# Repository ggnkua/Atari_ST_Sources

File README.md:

# Atari ST source code repository

## What is it?

A repository collecting source code for the Atari ST, STE, Mega ST, Mega STE, STBook, STacy, TT030 and Falcon030 ([Wikipedia link](https://en.wikipedia.org/wiki/Atari_ST)).

## How to get it?

Just clone the repository. Make sure to init the submodules while cloning (```--recurse-submodules```) so that you get the code from linked repositories.

## How to use the code on this archive?

TODO (tl;dr: get some dev tools and dig in!)

## How can I contribute?

1. Upload your source somewhere and raise an issue
1. E-mail the maintainer (ggnkua [at] gmail [dot] com) with archive(s) of files and optionally the location of the archive the files should be placed
1. Fork the repository and create a pull request (note that the maintainer has no experience with this and is likely to mess up things. But hey we can try!)

# Verified to compile

## ASM

## C

|Location|Comment|
|--|--|
|`C/Alan Pratt/Gulam`|Compiles with Mark Williams C 3.0.5|
|`C/Michael Thänitz/7UP_PD`|Compiles with Pure C|
|`C/Markus Kohm/7UP_PD`|Compiles with Pure C|
|`C/Paradox/X-Debug`|Builds with Lattice C 5.6 and DevPac 3.1|

## GFA Basic

## Omikron Basic

## Pascal

## STOS

## Various

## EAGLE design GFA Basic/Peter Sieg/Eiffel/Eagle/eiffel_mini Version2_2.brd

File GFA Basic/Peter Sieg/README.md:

# Atari-ST

```
Aus Wikipedia:  

Der Atari ST war ein Heimcomputer von Atari aus dem Jahr 1985. Die ST/TT-Serie eignete sich allerdings auch für professionelle
Büroanwendungen. Die Abkürzung "ST" steht dabei für Sixteen/Thirty-Two (16/32), da der verwendete Hauptprozessor, der Motorola
68000, einen 16 Bit breiten Datenbus hat und intern mit 32 Bit arbeitet. Der Adressbus ist 24 Bit breit. 

Geschichte

Der Atari ST war eines der ersten verbreiteten Modelle mit einer grafischen Benutzeroberfläche, dem GEM von Digital Research;
der Hauptspeicher lag zwischen 512 kByte und einem MByte, diese Zahl wurde, nach Aufrunden, Teil der Modellbezeichnung (520 ST
- 512 KB; 1040 ST - 1024 KB = 1 MB). Einzige Ausnahmen bildeten der 260 ST (wurde mit 512 KB ausgeliefert) und der 520ST+ 
(1 MB). Der 260 ST sollte getreu seiner Bezeichnung auch nur mit 256 KB ausgeliefert werden. In der Endphase der Entwicklung 
stellte sich jedoch heraus, daß 256 KB definitiv nicht ausreichen würden, um den Rechner mit TOS sinnvoll zu betreiben. Da 
jedoch die Werbetrommeln bereits gerührt wurden, wurde er kurzerhand mit 512 KB ausgeliefert. Da er sich sonst kaum vom 520 ST 
unterschied, verschwand er sehr schnell vom Markt. Zusätzliche Buchstaben gaben weitere Ausstattungsmerkmale an, der 1040 STF 
besaß etwa ein internes 3,5"-Floppylaufwerk und der 1040 STFM einen TV-Modulator. Anfangs wurde der Atari ST mit dem 
Betriebssystem auf Diskette ausgeliefert (TOS 1.0), spätere Modelle hatten das Betriebssystem fest im ROM eingebaut. Die Mega 
ST Serie besaß eine abgesetzte Tastatur und einen Hauptspeicher von bis zu 4 MB. Festplatten waren ebenfalls verfügbar (anfangs 
20 MB, MFM) und direkt an den Atari ST anschließbar (DMA-Port, auch ACSI-Port genannt). Der Atari ST besaß die Möglichkeit, 
entweder einen hochauflösenden Schwarzweiß-Monitor oder einen Farbmonitor mit geringerer Auflösung anzuschließen. Die 
Farbauflösung betrug 320×200 Pixel bei 16 Farben und 640×200 bei 4 Farben, jeweils aus einer Palette von 512 Farben. Der 
monochrome Monitor SM124 hatte eine Auflösung von 640×400 Pixeln bei 72 Hz Bildwiederholrate. Dies waren für die damalige Zeit 
hervorragende Werte, im PC-Sektor gab es gerade CGA, Hercules und für besonders teure Rechner EGA. Daher wurde der Rechner 
besonders im CAD- oder DTP-Bereich populär. Im deutschsprachigen Raum überwogen auch ansonsten eher Büroanwendungen wie 
Textverarbeitung oder Tabellenkalkulation. In den USA wurde der ST vorwiegend mit Farbmonitor eingesetzt und galt eher als 
Spiele- und Demomaschine (siehe: Atari Demos). Weltweit brachte dem Atari ST eine fest eingebaute MIDI-Schnittstelle eine weite 
Verbreitung bei Musikern und Tonstudios ein. Des Weiteren war der Atari ST sozusagen ein Mittler zwischen den Welten. Das 
Dateisystem der Disketten war mit dem von MS-DOS weitgehend kompatibel, so dass man beispielsweise Zugriff auf Textdateien 
hatte, die auf einem PC erstellt wurden. Es gab auch einen Apple-Emulator, und er wurde, mit entsprechender Software versehen, 
als intelligentes Terminal und Entwicklerstation an verschiedensten Mainframes und Mini-Computern von HP sowie Workstations von 
Texas Instruments und HP eingesetzt. Der Atari ST stand in Konkurrenz zum etwas später auf den Markt gekommenen Amiga 500 von 
Commodore. Als Nachfolgemodelle des Atari ST gab es noch den Atari TT, den 1040 STE, den Atari MegaSTE, den Laptop Atari STacy 
aber auch ein Notebook STBook und ab Anfang der 1990er den Falcon. Letzterer hatte dann aber keinen großen Markterfolg mehr. 
Mehrere Fachzeitschriften wie ST-Computer, ST-Format, ST-Magazin, TOS, XEST oder Atari Inside versorgten die Nutzer mit 
Informationen zu diesem Rechner. 

Hardware
Prozessor:             Motorola MC68000, 8 MHz 
Arbeitsspeicher:       512 bis 1 MB (max 4 MB über Speichererweiterungen von Drittanbietern möglich), 
                       von dem Speichercontrollerchip "MMU" verwaltet. 
Grafikchip:            "Shifter", benutzte eine Teil des Hauptspeichers als Bildspeicher, wird heutzutage als 
                       "Shared Memory Architektur" bezeichnet. Auflösungen und Farbtiefen siehe oben 
Blitter-Chip:          Erst ab 1040STFM, Unterstützung der CPU bei Grafik- und Speicheroperationen. 
                       Nachrüstung über Zusatz-Karten in allen ST-Modellen möglich. 
GLUE-Chip:             Systemlogik, die das System zusammenhält (Chip-Selects, Takt, etc.) 
Sound:                 Yamaha YM-2149, dreistimmiger Synthesizer-Chip mit Rauschgenerator 
Floppy-Controler:      WF1772: MFM-Controller für Laufwerke mit Standard-Shugart-Bus. 
DMA-Controller:        von Atari, steuert die ACSI-Schnittstelle (Atari Computer System Interface) an. 
                       ACSI ist eine auf Gruppe-1-Kommandos und einige Signale eingeschränkte SCSI-Schnittstelle. 
2x Motorola 6850:      Interface-Bausteine, 1x für die Midischnittstelle, 1x für die serielle Kommunikation mit der 
                       Tastatur 
MFP:                   68901 MFP (MultiFunctionPeripheral) u.a. für erweiterte Interruptlogik und serielle Schnittstelle 

Modelle
Modell    Jahr Merkmal 
260 ST    1985 Ur-ST mit Disketten-TOS, nur sehr kurz auf dem Markt 
520 ST    1985 Ur-ST mit Disketten-TOS 
520 STM   1985 ROM-TOS, TV-Anschluss - wurde später in 520 ST umbenannt
               Preis inkl. SF354+SM124 2.000DM (1.020€)
 
520 ST+   1985 1 MB RAM 
520 STF   1986 internes Diskettenlaufwerk 
520 STFM  1986 wie 520 STF, mit TV-Anschluss 
1040 STF  1986 wie 520 STF, 1 MB RAM 
               Preis inkl. SM124 ca. 3.300DM (1.700€)
 
1040 STFM 1986 wie 1040 STF, mit TV-Anschluss 
2080 ST   1986 „Prototyp“ - 2 MB RAM 
4160 ST   1986 „Prototyp“ - 4 MB RAM 
MEGA ST   1987 abgesetzte Tastatur, 1, 2 oder 4 MB RAM 
4160 STE  1988 „Prototyp“ - um Stereo, 2 Joypad-Ports, BLiTTER erweitert 
1040 STE  1989 Final Version des 4160 STE, nur 1 statt 4 MB RAM
               Preis ca. 1.300DM (660€)
 
520 STE   1989 Wie 1040 STE, 512 KB RAM 
1040 STE+ 1990 Prototyp - 1040 STE mit Festplatte und AT-Emulator 
TT 030    1990 68030-CPU/32 MHz, neues TOS 3.0 
Mega STE  1991 erweiterter Mega ST im TT-Gehäuse, TOS 2.0x, 16 MHz. Preis für 4MB Version: 2.800DM (1.400€)
 
FX-1      1991 Falcon-Prototyp mit TOS 2.07 
Falcon030 1992 68030-CPU/16 MHz, 56k-DSP, TOS 4.0x, 1040ST-Gehäuse
               Preis für 4MB+85MB HDD Version: 2.250DM (1.150€)
 
Falcon040 1993 „Prototyp“ - Falcon mit 040-CPU 
Microbox  1993 „Prototyp“ - Falcon im Desktop-Gehäuse 
Tragbare Modelle
Modell    Jahr Merkmal 
Stacy     1989 7,5 kg schwerer Laptop auf Basis des Mega ST 
ST Book   1991 Grundfläche eines DIN-A4-Blatts, knapp 2 kg leicht; ca. 1000 gebaute Einheiten 
ST Pad    1991 'Prototyp' - Pentop-Computer 

Tipps

PC Floppy's sind auf ID=1 eingestellt. Atari ST benötigen ID=0! Dies kann man umstellen (Jumper, Lötbrücke, etc.). 

Oft gestellte Frage: Wie bekomme ich die Dateien von meinem Windows-PC auf meinen Atari-ST? 

Oft hat der Windows-PC hat Probleme auf dem Atari ST formatierte Disketten zu lesen/schreiben. Die einfachste Lösung ist es die Disketten auf dem Windows-PC zu formatieren! Sollten Sie keine DD-Disketten auftreiben können, nehmen Sie HD-Disketten und kleben Sie das zweite Loch (das ohne Schreibschutz-Schieber) mit Klebeband ab.
Nun muß die Diskette nur noch als DD-Diskette formatiert werden. 

MS-DOS / Windows95/98:
In die Kommandozeile/DOS-Shell gehen und formatieren: format /F:720 a: 

Windows XP:
Leider kennt der format-Befehl unter Windows XP den obigen Parameter nicht mehr :-( Aber der folgende Aufruf tut das selbe: format /T:80 /N:9 a: 

Hi, die einseitigen Laufwerke gab es nur als Externe Laufwerke SF354..
Diese wurden 1985 mit den ersten 520ST ausgeliefert.. 

520ST 512kb mit Disk-Tos, im Rom nur ein Loader...
SF354 360k Einseitig...
Monochom Moni... 

Gesamt 3000.- DM 

kurze Zeit später wurden die ersten SF314 ausgeliefert.... 

Alle ST mit eingebauten Laufwerken waren dann 720k-Laufwerke... 

Disk mit mehr als 720k waren überformatiert..... 

Reparatur Tips

Leblos liegt er da, mehrfaches Ein- und Ausschalten ruft nur eine schwache binäre Reaktion hervor: die LED für die 
Betriebsanzeige signalisiert "Strom", oder eben nicht.
Nach kräftigem Schütteln des Patienten der erste Hoffnungsschimmer, der Monitor wird weiß. Dabei bleibt es leider auch. 
Also nochmal aus- und wiedereingeschaltet ... nichts. Der letzte zögerliche Kontaktversuch unseres digitalen Kameraden 
lässt sich offensichtlich nicht reproduzieren. Wie gut hat es dagegen der Bekannte X getroffen, der hat wenigstens Bomben 
auf dem Bildschirm, 'mal zwei, 'mal drei und manchmal eine ganze Reihe.
Diese Symptome offensichtlicher Altersschwäche sind in letzter Zeit immer häufiger geworden. Die Ratlosigkeit von 
Computerfachhändlern angesichts eines Atari-Rechners weckt nicht gerade Vertrauen in die Kompetenz derselben. Zudem 
rechtfertigt der Wiederbeschaffungswert beispielsweise eines 1040 ST von ca. DM 250,- in den seltensten Fällen 
dreistellige DM-Aufwendungen für die Reparatur. Also, Ärmel hoch, denn die Axt im Haus ...
Um Mißverständnissen vorzubeugen:
Schwerwiegende Defekte können auch nach Studium dieses Artikels nicht von Laien behoben werden. Es hat sich jedoch 
gezeigt, dass ca. 80% aller Funktionsstörungen sehr einfache Ursachen haben, die meist leicht behoben werden können. 
Hier soll gezeigt werden, wie man die eine oder andere Störung mit wenig Aufwand beseitigen kann.
Zur Sache
Hier einige häufige Fehler und deren vermutliche Ursache, in Klammern die Absätze, die man mindestens lesen sollte:
   1. Betriebsanzeige leuchtet nicht > Netzteil defekt (A, B1)
   2. Bildschirm bleibt schwarz > Kontakt /RAM-Fehler (A, C, D)
   3. Bildschirm bleibt weiß > Kontaktfehler (A, C)
   4. Pixelmüll > Kontakt /RAM-Fehler (A, C, D)
   5. Rechner stürzt bei Anfahren der Menüleiste ab (Mega ST) > Blitter (A, E)
   6. Rechner stürzt nach gewisser Zeit ab > Kontakt /RAM-Fehler (A, C, D, Netzteil B2)
   7. Rechner hängt bei Floppyzu griffen > Netzteil (A, B2)
   8. Uhr läuft nicht richtig, Rechner bombt willkürlich > Echtzeituhr (A, F) 
Noch ein Hinweis:
Rechner mit diversen Erweiterungen können auch diverse erweiterte Probleme mit sich bringen, auf die hier im Einzelnen 
nicht eingegangen wird. Sicher ist aber in jedem Fall, dass eine Hardwareerweiterung, gleich, welcher Art, nur in einem 
einwandfrei funktionierenden Rechner richtig arbeitet.
A: Öffnen des Rechners
Rechner auf den Rücken legen, alle Schrauben lösen und beiseite legen. Wieder umdrehen und Deckel abheben. Beim 260/520 
einfach nach oben weg, beim 1040 zuerst an der Seite ohne Floppy, beim Mega ST zuerst hinten und die Leitung zum 
Batteriefach abziehen. Es sollte keine Diskette im Laufwerk sein, damit der Auswurfhebel nicht stört.
Beim 260/520er und 1040er die Tastatur abziehen und die drei Schrauben an der vorderen Blechkante lösen. Die Platine des 
260/520ers ist noch mit drei weiteren Schrauben befestigt, die man durch Öffnungen im Abschirmblech erreicht, weg damit. 
Besitzer eines 1040 müssen die beiden Schrauben mit denen das Netzteil befestigt ist, lösen. Die Platine wird nun mitsamt 
Abschirmblechen aus dem Plastikunterteil gehoben.
Ein Mega ST kann in seiner Behausung verbleiben.
Jetzt mit einer Flachzange die Blechlaschen geradegebogen, bei 1040 und Mega ST ist auch eine unter der Floppy, und das 
obere Abschirmblech lässt sich abnehmen. Das Netzteil des 1040 ist dabei etwas im Wege, aber es ist zu schaffen.
Das war es, für den Zusammenbau einfach den Text rückwärts lesen.
B1: Das Netzteil
Wenn das Netzteil ausgefallen ist, sollte man sich nach einem Ersatz umsehen. Beim 520er ist der Trafo vergossen und 
deshalb unzugänglich, bei 1040 und Mega ST handelt es sich um Schaltnetzteile. Der Fachmann weiß: selbst wenn man ein 
defektes Bauelement findet und ersetzt, heißt das noch lange nicht, dass das gute Stück wieder funktioniert. Man kann 
bestenfalls die Sicherung überprüfen und bei Defekt ersetzen. Mir ist bisher allerdings noch kein Netzteil untergekommen, 
das durch Austausch einer defekten Sicherung wieder zu reaktivieren war, als einziges Ergebnis meiner Bemühungen hatte 
ich dann mehrere defekte Sicherungen.
B2:
Die Netzteilspannung sinkt offenbar mit zunehmendem Alter des Rechners ab. Wichtig ist vor allem, dass im 5Volt-Zweig die 
Spannung nicht zu niedrig ist.
Die meisten Bauelemente im Atari benötigen eine Spannung von minimal 4,5 V und maximal 5,5 V. Mit einem Handmultimeter 
lässt sich das überprüfen. Aber Achtung! Bei Floppyzugriffen sinkt die 5-Volt-Versorgungsspannung um ca. 0.4 Volt ab. Das 
bedeutet, das für einen sicheren Betrieb eine Spannung von 4,9 Volt anstehen muss.
Ein zu schlappes Netzteil kann auf folgende Weise getuned werden: man lasse sein Multimeter zur Kontrolle an der 
5 Volt-Versorgung hängen und suche ein Poti namens VR1. Wenn man eines gefunden hat, kann man damit die Spannung 
abgleichen. Leider läuft der 12 Volt-Zweig auch mit, so dass man zwischendurch auch dort 'mal die Spannung kontrollieren 
muss. Wenn 13 Volt überschritten werden, sollte eine Diode 1N4001 in die 12 Volt Leitung eingeschleift werden. Der 
Kathodenring in Richtung Board.
Wer in seinem Netzteil kein Poti findet weil keines da ist, muss parallel zu R14 einen Widerstand von 47K einlöten.
C: Kontaktfehler
Kontaktfehler sind die häufigste Ursache für "seltsame Erscheinungen". Ob es sich dabei um Oxydation, Verschmutzung oder 
ausgeleierte Kontakte handelt ist eigentlich egal, der Effekt ist immer der gleiche.
Bei einem weißen Bildschirm ist zumindest das RAM ansprechbar. Der Fehler ist aller Wahrscheinlichkeit nach bei den Roms 
zu suchen. Also, Spucke auf den Daumen und die "Brüder" kräftig in die Fassungen gedrückt.
Wenn man schon mal dabei ist, sollte man auf ein Nachdrücken der anderen Bauelemente nicht verzichten. Hat diese 
fachmännische Aktion keine Früchte getragen, ist man gezwungen sich mit dem GLUE zu befassen. Beschreibung weiter unten.
Bei einem schwarzen Bildschirm sieht die Sache von Vornherein etwas schwieriger aus. in diesem Fall muss man sich mit der 
MMU auseinandersetzen. Es handel sich dabei, wie bei dem GLUE, um einen quadratischen Chip mit 68 Pin's im PLCC-Gehäuse. 
Die MMU hört auf den Namen C025912, der GLUE auf C025915. Eventuell vorhandene Klammern über den Chips werden entfernt, 
indem mit einem kleinen Schraubendreher eine Seite
der Klammer vorsichtig über die Sockelecke gehebelt wird. Wenn kein zusätzliches Blechkreuz über den Sockel gespannt ist 
und man auch keines zur Hand hat, verzichtet man besser auch auf den Einsatz der Klammern.
Durch die Verspannung des Sockels kann es schon zu Problemen kommen, die Chips fallen auch so nicht heraus. Aber weiter 
im Text: sowohl MMU als auch GLUE haben dann und wann unter Kontaktarmut zu leiden. Bei beiden macht es sich am besten, 
sie einmal aus ihrem Sockel zu hebeln und wieder hineinzustopfen.
Normalerweise wird dafür ein PLCC-Ausziehwerkzeug benutzt. Diese hat aber nicht jeder im Hause. Deshalb muss der gute 
alte Uhrmacherschraubendreher mit 1mm Klinge einspringen.
Also: Die Klinge in eine der Aussparungen im Sockel stecken und den Chip heraushebeln, das gleiche Spiel diagonal 
gegenüber wiederholen.
Jetzt die Anschlüsse kontrollieren, gegebenenfalls wieder geradebiegen und den Chip zurückstecken. Pin 1 ist durch eine 
kreisförmige Vertiefung gekennzeichnet.
Wer nun eine Verbesserung/ Veränderung, aber noch keinen sicheren Betrieb feststellt, sollte die Kontakte von MMU und 
GLUE mit einer feinen Drahtbürste reinigen, die Kontakte in den Sockeln natürlich auch.
Pixelrnüll hat seinen Ursprung in der Regel in schlechter Verdrahtung oder falscher Einbaulage von Speichererweiterungen.
In jedem Fall müssen die Leitungen so kurz wie möglich sein und an der Zahl der Masse- und +5-Volt-Leitungen sollte man 
nicht sparen.
Lässt sich bei den Leitungslängen nichts mehr "herausholen", kann man durch Einschleifen eines Treibers in die 
Steuerleitungen Ras, CasL, CasH und WE die Flankensteilheit so verbessern, dass der Betrieb wieder sicher ist.
Verwendbar ist z.B. ein 74F125. Pin 14 = +5 Volt
Pins 1, 4, 7, 10 und 13 auf Masse Eingang > Ausgang: 2>3,5>6,9>8,12>11.
D: RAM-Fehler, oh Graus...
Schwer zu lokalisieren und genauso schwer zu beheben, deshalb nur 'was für Atarianer mit Bastelerfahrung. Auch Besitzer 
eines 520er ohne Speichererweiterung haben hier schlechte Karten.
Beim Einschalten prüft der Rechner seine RAM-Konfiguration. Er klappert dabei die beiden RAM-Bänke 0 und 1 ab und muss 
mindestens auf Bank 0 ein wenig RAM finden, um hochzulaufen. Wenn nun gerade auf Bank 0 ein Speicherchip defekt ist, 
bleibt der Bildschirm schwarz, der Atari hat kein RAM.
Hat man zufällig auch die Bank 1 mit RAMs bestückt, wie es im 1040 und Mega ST der Fall ist, kann man die Widerstände der 
Steuerleitungen ramseitig auslöten und der jeweils anderen Speicherbank zuordnen. Es ist sehr unwahrscheinlich, dass auf 
beiden Bänken ein Chip defekt ist.
Für diese Aktion ist ein Ohmmeter unerläßlich, Lötkolben, etwas Kabel usw. sind ebenfalls Voraussetzung.
Interessant sind die Widerstände mit 68R (blau, grau, schwarz, gold) in der Nähe der RAMs. Sechs sind es an der Zahl und 
meist in zwei Gruppen von je drei Stück aufgeteilt. Diese sind alle mit Pins der MMU verbunden, und zwar an folgende:
Pin 6 = Cas0H Pin 7 = Cas0L
Pin 8 = Ras0 Pin 18 = Rast
Pin 21 = Cas1L Pin 22 = Cas1H
Zur Sicherheit von diesen Pins der MMU ausgehend mit dem Ohmmeter die entsprechenden Widerstände lokalisieren.
Alle Widerstände auf der RAM-Seite auslöten oder kurz über der Platine abkneifen. Das nun unbewohnte Lötauge Ras0 
ramseitig mit +5 Volt verbinden, dadurch wird die RAM-Bank 0 lahmgelegt. Jetzt die für die Bank 0 vorgesehenen freien 
Widerstandsenden mit den freien Lötaugen der Bank 1 verbinden, Ras0-Signal an RastLötauge usw. Wenn der Rechner nun 
wieder läuft, hat er natürlich weniger RAM, also die Signale der Bank 1 mit der RAM-Bank 0 verbinden (+5V-Leitung 
entfernen) und 'mal sehen, was passiert.
Aller Wahrscheinlichkeit nach wird der Rechner normal arbeiten und die Speicherbank mit dem defekten Chip nicht erkennen, 
aber manchmal hat man Glück. Sollte der Rechner diese Bank akzeptieren, gibt sich der Übeltäter als Pixelfehler auf dem 
Bildschirm zu erkennen. Jetzt kann man entweder auf dem Monitor Pixel zählen, oder sich der Holzhammermethode bedienen: 
Man nehme eine Meßstrippe und lege eine Seite auf Masse. Dann tippe man mit dem anderen Ende auf den Datenpin eines RAM 
der defekten Bank.
Meistens "steht" der Rechner dann, aber das Monitorbild ist nach wie vor zu sehen. Wenn man mit der Meßspitze nun einen 
Datenpin nach dem anderen berührt, sieht man auf dem Monitor senkrechte weiße Linien. Sobald sich diese Linien mit den 
Pixelfehlern decken, ist der defekte Chip gefunden.
Datenpins bei X1256 = Pin 2 bei
X11000 = Pin 1 bei
X4256 = Pin's 1, 2, 18, 19.
Wer über ein entsprechendes Testprogramm verfügt, kann sich zumindest den letzten Teil der Arbeit sparen.
E: Der Blitter
Schuld an solchen Boshaftigkeiten ist normalerweise der Blitter. Als Grafikchip für rechteckige Datenschiebereien 
zuständig, hat er genau dann seinen ersten Einsatz. Also probehalber erstmal 'raus damit.
Dazu wie unter C beschrieben das IC aus dem Sockel befreien. Noch ein Tip zur Position: der Blitter liegt zwischen 
Mega-Bus und Romport und ist "ein quadratischer Bursche". Wer jetzt den Rechner einschaltet, wird ein langes Gesicht 
machen, weil nichts geht. Geduld bitte...
Da vom Blitter ein Signal weitergereicht wird (was er natürlich nicht mehr tut, wenn er nicht mehr da ist) müssen noch 
zwei Lötbrücken geschlossen werden. Eine liegt links vom Mega-Bus und eine ca. 2cm oberhalb.
Wenn das erledigt ist, sollte der Rechner wieder laufen. Nach Einbau eines intakten Blitters das Öffnen der Lötbrücken 
nicht vergessen!
F: Das leidige Bomben
Nicht ganz so häufig, aber trotzdem ärgerlich. Schuld ist ein Kondensator: Name C52, Sollwert 100nF.
Im Gegensatz zu den meisten anderen 100nF - Kondensatoren auf der Mega-ST-Platine realisiert dieser, zusammen mit einem 
10K-Widerstand, ein Zeitglied. Damit wird verhindert, dass in der Power-Up-Phase irgendwelcher "Kram" in die 
Uhrenregister geschrieben wird. Den Kondensator nun durch einen neuen ersetzen und das war's mit hoher 
Wahrscheinlichkeit.
Ich bin hier bei Weitem nicht auf alle möglichen Fehlerquellen eingegangen, aber für weitergehende Reparaturarbeiten ist 
schon eine kostspielige Ausrüstung erforderlich.
us
Reparatur Tips 2
================
            Verschiedene kleinere Hardwaredefekte der ST Serie
           ..................................................
 An alle die User die mit ihrem Rechner irgenwann einmal probleme hatten
 und eine Menge Geld bei der Reperatur gelassen haben,denn für manch eine
 Reperatur bekommt man einen Funktionsfähigen gebrauchten Rechner !
   -------------------------------------------------------------------------
 - Symtom     : Verschiedene schwarze Pünktchen auf dem Bildschirm
   Ursache    : Eventuell Ramfehler
   Beseitigung: Mit dem Atari Testkit (ab V3.3) wird warscheinlich ein
                Ramfehler U19  Bit Nr.5 in der Bank 0 angezeigt.......
                (Die Profis schreiben ein Basicprogramm mit dem sich die
                einzelnen Bit's austesten lassen.)
   Abhilfe    : U19 defekt,Baustein austauschen
   -------------------------------------------------------------------------
 - Symtom     : Bild läuft durch und die Floppylaufwerke werden nicht mehr
                angesprochen,fehler tritt meist bei System 260/520 auf.
   Ursache    : Zu 90% Baustein U35 defekt..
   Beseitigung: Komplett austauschen
   -------------------------------------------------------------------------
 - Symtom     : Bildschirm ist komplett mit der Farbe rot,grün oder blau
                gefüllt.
   Beseitigung: J9 Anschlussbuchse überprüfen und eventuell kontakte
                nachlöten. (Nicht 1040 u. Mega)
   -------------------------------------------------------------------------
 - Symtom     : Weisse Punkte auf dem Bildschirm (Mono/Color) beim Mega ST
   Ursache    : Warscheinlich thermische fehler an den Bustreibern
                74LS244 oder/und 74LS373 .......
                Rambausteine nicht richtig in den Sockeln
   Abhilfe    : Treiberbausteine mit Kältespray untersuchen
   Beseitigung: Bausteine auswechseln / Ram's in die Sockel drücken
   -------------------------------------------------------------------------
 - Symtom     : Nach dem Einschalten des Computers sind auf dem Monitor
                rücklaufstreifen zu sehen     (SM124)
   Ursache    : meist ist der Widerstand R727 zu hochohmig...
   Beseitigung: R727 gegen einen Widerstand von 560Kohm austauschen.
                Kleine änderung der Grundhelligkeit an Poti VR702 (Sub-Right)
   -------------------------------------------------------------------------
 - Symtom     : Das Bild auf dem SM 124 ist nur noch halb so hoch wie
                normal,wirkt aber wesentlich breiter..
   Ursache    : +12V Stromversorgung eventuell defekt
   Beseitigung: IC 901 und Q 901 überprüfen und gegebenenfalls austauschen.
                +12V überprüfen Toleranz +/- 15%
   -------------------------------------------------------------------------
 - Symtom     : Helligkeit lässt sich nicht mehr aufregeln (SM124)
   Beseitigung: Transistor Q303 im Videoteil überprüfen / austauschen
                An den Spannungsteilern sollten zu messen sein
                R310 = 8V   R302 = 3.6V
   -------------------------------------------------------------------------
 - Symtom     : Nach einiger Zeit bringt der Computer kein richtiges Bild
                mehr auf den Bildschirm   ...(Monitor in Ordnung!)
   Ursache    : Treiber in der V-Sync. leitung überprüfen (74LS04) und
                Shifter testen...
   Beseitigung: Die Bausteine mit Kältespray überprüfen
   -------------------------------------------------------------------------
 - Symtom     : Nach Anschluss einer Harddisk oder eines Laserdruckers
                stürtzt das System ab und/oder lässt sich nicht booten.
   Ursache    : Das Reset-Signal wird im ST mit hilfe eines NE 556 bzw.
                TL 7705 erzeugt und über treiber an die Bausteine und die
                externen Anschlüsse geleitet. (HD-Port)
   Beseitigung: Einbau eines kleinen Filter in Pin 12 des HD-Port...
                Es können Störspitzen über die Kabel zurück in den Rechner
                gelangen,dadurch erhält der Computer undefinierte Reset's
                die zu den Störungen führen. Tritt häufig bei zu langen
                DMA-Kabeln auf.
                (Bei SH 205 eventuell ausfall des Reset-eingangs (47LS123))
   -------------------------------------------------------------------------
 - Symtom     : Bildschirm bleibt immer Dunkel
   Ursache    : meist Treiberbaustein 74LS04 defekt... (7404 bei Mega St)
                und Midi-Benutzern.
   Beseitigung: Mal an den reset und halt eingängen des Prozessors messen...
                Normal sind hier 0 oder 5V. Liegen die Spannungen zwischen
                diesen werten so ist der Treiber 100% defekt...
                Dieser Treiberbaustein bedient auch die Midi-out Leitung.
                 Wie mach ich meinen Rechner kaputt... ?
                 --------------------------------------
 Sollte sich der Atari ab und zu ohne erkennbaren Grund verabschieden
 mit Bomben oder selbständigen Reset,so ist es sinnvoll sich zuerst den
 Monitorstecker genau anzusehen.
 Der Monitor legt den "MonoDetect-Pin" auf einen 0V pegel(Masse)
 Ist diese Steckverbindung nicht mehr optimal,reich oft schon ein Stoss
 an das Tischbein um den Rechner austeigen zulassen.
 Meistens genügt ein LEICHTES verbiegen der Stifte im Stecker oder ein 
 eventuelles Nachlöten der Monitorbuchse im Rechner.
 Auch die meist schlechte befestigung der internen Abschirmbleche
 (die sowieso kein Mensch braucht)
 sind oft ein grund für selbständige Reset's.
 Man muss sie dann entweder sehr gut befestigen oder ganz entfernen,
 was auch der Luftzirkuation im Rechner keinen Abbruch tut,eher das
 Gegenteil.....
 Bei den älteren Modellen 520/520+ kommt es meisst nach langem Dauer-
 betrieb zu einigen Bildstörungen.
 Man kann diesen Fehler mit Kältespray sehr leicht finden,zuerst wird
 der Shifter mal eingesprüht,verbessern sich die Bildfehler ist der
 Unruhestifter gefunden.
 Zur weiteren Abhilfe kann man den 47pF - Kondensator der zwischen Pin 39
 des Shifters und Masse liegt, entfernen und unter Umständen wieder 
 zwischen Pin 11 und Masse einlöten...
 Dazu sind einige Versuche nötig.
 Danach sollte dann auch bei warmem Rechner ein Einwandfreies Bild zu
 sehen sein....
 
 Jetzt mach ich es Schneller.....
 Da Atari keine eigenen Laufwerke baut, gibt es in den Rechnern Laufwerke
 der verschiedensten Hersteller
 Meist sind es bei den älteren Modellen Epson Laufwerke.
 Danach gab es Laufwerke von Chinon und Mitsubishi und ähnlichen
 krempel,eines haben die Laufwerke alle gemeinsam:
 Die Unterschiedliche Drehzahl des Antriebsmotors.
 Es gibt natürlich noch jede Menge Laufwerke anderer Hersteller die als
 sogenannte Fremdfloppys an den ST Rechnern verwendung finden.
 NEC / TEAC / SONY / BASF usw.
 Die eigentliche Drehzahl eines jeden Laufwerkes sollte sich zwischen
 299 - 300 - 301 Upm bewegen,jede Abweichung dieser Drehzahl ist ein 
 Griff in's Klo....
 Das heist es kommt dann meist zu Lesefehlern,oder man kann die Disk's
 von anderen Rechnern nicht lesen...
 Es gibt auf dem PD Sektor bereits seit einiger Zeit Programme mit denen
 die möglichkeit besteht die Drehzahl eines Laufwerkes zu justieren.
 Allerdings muss dann auf der Platine des Floppies, das entsprechende
 Poti gesucht und gefunden werden.
 Auch das Scheibenkleister Buch ist eine grosse Hilfe.
 Von jedem Laufwerk hier eine Beschreibung zu geben würde warscheinlich 
 die Box sprengen.
 Anmerkung:
 Dieses "Justierpoti" gibt es nicht in allen Floppy's,bei manchen muss man
 ein Kondensatorchen verändern.
 Ausserdem ist das etwas,wo man nicht unbedingt seine Finger reinstecken
 sollte! Der Fachmann kann das besser!!
 Ein anderes Problem sind die ssinger", gemeint sind einige Modelle des
 1040 ST,besonders die älteren....
 Da gibt es auf der Hauptplatine einen Schwingkreis (schönes Wort,gell ?)
 Das Teil liegt in der Nähe des IC TL 497 .Da gibt es einen Widerstand
 R 17 und die Spule L4 sowie den Kondensator C28 .....
 (das ist der ganze Krachmacher)
 R17 wird einfach durch einen 5 Ohm - Widerstand ersetzt L4 wird auf
 210 uH (Microhenry) geändert und C28 wird auf 330 pF erhöht....
 und schon herscht traumhafte Stille im Kasten!
 Zu suchen sind auch nach sogenannten Resonazschwingern,das können
 Blechteile und sonstwas sein (Netzgerät) lose Drähte,die durch das
 Laufwerk im Rechner zum Schwingen Angeregt werden.
 
 Schwach auf der Brust ?
 Manche Netzteile der ST Serie gehen bei der kleinsten Hardware
 erweiterung in die Knie,das ist ausgesprochen schlecht !
 Meist äussert sich das dann mit irgenwelchen Zicken die der Rechner
 vorher nicht gemacht hat.
 Zur Abhilfe könnte man genügen grosse Pufferelkos in das Netzteil 
 einlöten (zusätzlich) da die Belastung des Netzteiles im Einschaltmoment
 doch ganz erheblich ist.
 Natürlich steht der Verwendung eines Schaltnetzteil nichts im Wege,
 vorausgesetzt die Spannungen stimmen.
 Doch Vorsicht mit Basteleien an Netzteilen und anderen Powie's...!!!!
 Auch das einlöten von zusätlichen Elkos sollten Leute machen die die
 Materie beherschen .....
 Ein verpolter Elko hat die Wirkung und Reichweite eines Kanonenschlages!!
 Die Dimensionierung könnte in der 4700 uF 40V Klasse liegen...
 Auch der Austausch der Gleichrichterbrücke gegen eine stärkere bewirkt
 manchmal kleine Wunder.
 Zu beachten wäre noch das bei primärgetakteten Netzteilen die
 Brücke für 220V bemessen werden muss.
 
 Fehler über Fehler...
 
 Das allerbeste in den ST's sind die IC Fassungen,hier hätten ein paar
 gute Sockel den Preis dieses Rechners wohl kaum in die Höhe getrieben.
 Die häufigste Fehlerquelle ist das korridieren der kontakte,dann muss
 der entsprechende Chip vorsichtig aus der Fassung gehebelt werden
 und die (Kontakte) mit Spiritus oder etwas Alkohol gereinigt werden.
 Den Chip am besten im nassen Zustand wieder in die Fassung zurück
 stecken,Kontaktspray und Reiniger sind hier weniger gefragt,da ich
 feststellen musste das die Fassungen nach kurzer Zeit wieder vergammelt
 waren.
 Sollte es mal erforderlich sein einen Eingelöteten Chip wechseln zu 
 müssen sollte man gleich Sockel mit gedrehten und vergoldeten Pins
 Einlöten, die gibt es sogar als Chip-Carrier für die 
 Quadratischen Flundern....
 Auch das nachträgliche Festdrücken oder nachlöten einiger Chip's
 hat schon Wunder bewirkt.
 Das Auslöten fängt man am bestem mit dem Abzwicken aller Beinchen an,
 da die Atari Platinen an manchen Stellen Empfindlich gegen Hitze sind,
 ist der Chip komplett raus saugt man die Beinchen einfach mit einer
 Lötpumpe aus den Löchern und die Platine bleibt heil.
 (Im Gegensatz zu manchen Heissluftlötern) Argghhhh.....
 Natürlich ist der Chip dann im Eimer,aber das ist er meist sowieso....
 
 Lauter Miefquirl ....?
 Bei den meisten Festplatten ist der Lüfter genauso laut wie Mutter's
 Hoover....
 Die sicherste lösung diesen Nervtöter leise zu bekommen ist,sich im 
 Elektronikladen an der Ecke für 0,90 einen Festspannungsregler der
 Gattung 78xx zu besorgen,zur verwendung kämmen welche mit der
 Ausgangspannung von 8 oder 9 V.
 Dieser Regler wird in die 12V Zuleitung des Lüfters geschaltet,so das
 der Krachmacher nur noch mit 8 oder 9V läuft,das hat einen kleineren
 Luftstrom,folglich auch ein kleineres Arbeitsgeräusch zur Folge.
 Den Regler am besten so montieren, das er ebenfalls im Luftstrom
 gekühlt wird....
 Und für die Wärme der Platte reicht das allemal noch.
 Natürlich kann man die Lauten Atari Lüfter mal gegen einen PAPST-
 Lüfter austauschen,auch das hilft meist...
  
 No Floppy's..........??
 Sagte das Testmodul,nachdem man verzeifelt alle möglichen Ursachen für
 das nicht funktionieren der Diskettenlaufwerke gesucht hatte...
 Das ist eine Reperatur die im Fachbetrieb so ca. 300 DM kostet,im prinzip
 aber einfach ist.
 Die erste Möglichkeit: Die Floppys werden noch selektiert und laufen an,
 rattern aber irgendwan an den mechanischen anschlag.
 Das könnte bedeuten das der Floppycontroller und der Soundchip noch
 in Ordnung sind.
 Der Desktop erscheint sofort und ohne Icons...
 Rechner einschalten (ohne Diskette) und warten bis die Icons erscheinen,
 dann Testen ob die Laufwerke noch formatieren.
 Wenn das Formatieren nicht klappt so ist mit Sicherheit ein neuer DMA-Chip
 fällig,mit 100% Sicherheit wenn auch die Harddisk stumm bleibt...
 Auch ist es möglich das sich der Rechner nach dem Einschalten,sich so
 mit 2-30 Bomben meldet
 Die zweite Möglichkeit:
 Der Heissgeliebte WD 1772 muss nicht unbedingt defekt sein........
 er hat einen nachgeschalteten Treiber der Serie 74LS06....
 Write Data / Step / Direction / Motor On / Write Gate /
 das sind so die wichtigen Signale die über diesen Treiberbaustein
 gejagt werden.
 Ist der Treiber nun defekt fehlen diese Signale ganz oder teilweise,
 machen die Diskettenlaufwerke nur unsinn.
 Mit einem Preis von DM 1 ist das einer der Billigsten Chip's die 
 durch eine Fehlbeschaltung von aussen Zerstört werden kann.
 Man kann mit einem einfachen Logiktester dessen Funktion überprüfen,
 besser und sicherer ist allerdings ein Ozillo....
 Durch schwere Kurzschlüsse am Floppyport sind meist der Treiber und der
 WD 1772 fällig.
 Sollte sich heraustellen das die Laufwerke nicht richtig selektiert
 werden ist eine überprüfung des Soundchips YM 2149 unumgänglich.
 Die Signale Drive 1 Select / Drive 0 Select / Side 0 Select  werden 
 direkt und ohne Treiber vom Soundchip verwaltet.
 Die Pin's  Read Data / Index / Write Protect / Track 00 / liegen ohne
 Treiber wiederum direkt am WD 1772.......
 Man muss dann schon mal genau messen,was wann passiert.
 Meist ist es aber der DMA oder der WD und/oder dessen Treiber.
 Die schnellste methode ist einfach erst mal den Treiber auslöten,
 einen Sockel drunter und mit einem Frischen Chip bestücken....
 Wer oft die Floppystecker wechselt (Ein oder Austeckt) kann zudem noch
 mit kalten Lötstellen an ebensolcher rechnen....
 (Fernost Klebung)
 
 Druck auf allen Schläuchen......
 Der Drucker macht keinerlei Anstalten zu drucken ....?
 Ist bestimmt ein Japanischer........WEGWERFEN !
 Die komplette Centronics-Schnittstelle wird vom Soundchip YM 2149
 betrieben,sodas eine überlastung an dieser durch alte Drucker direkt
 zur Zerstörung führen kann.
 Die meisten älteren Drucker belasten diese Schnittstelle durch ihre
 Internen Pullup Widerstände so,das ein erhöhter Strom fliesst der dann
 den Port B des Soundchip's zerbröseln lässt.
 Abhilfe kann man durch eine extern Aufzubauende Treiberstufe schaffen,
 die alle Signale der Centronics-Schnittstelle entsprechend verstärkt,
 oder die Internen Pullup's des Druckers auslöten und durch entsprechend
 grössere Ersetzt.
 Normal wäre ein Wert so um die 3,3 KOhm.....alles was kleiner ist 
 könnte schädlich sein.
 Da der Soundchip meist nicht gesockelt ist,fallen auch hier einige
 Lötarbeiten an.
 Die,genau wie an allen andern Lötstellen besonders sorgfältig ausgeführt
 werden müssen.
 Am besten sofort einen Sockel mit gedrehten Pin's her und eingelötet,
 dann geht es beim nächsten Mal einfacher.....
 
 Don't Panic
                to be continue .....
Max Headroom
```

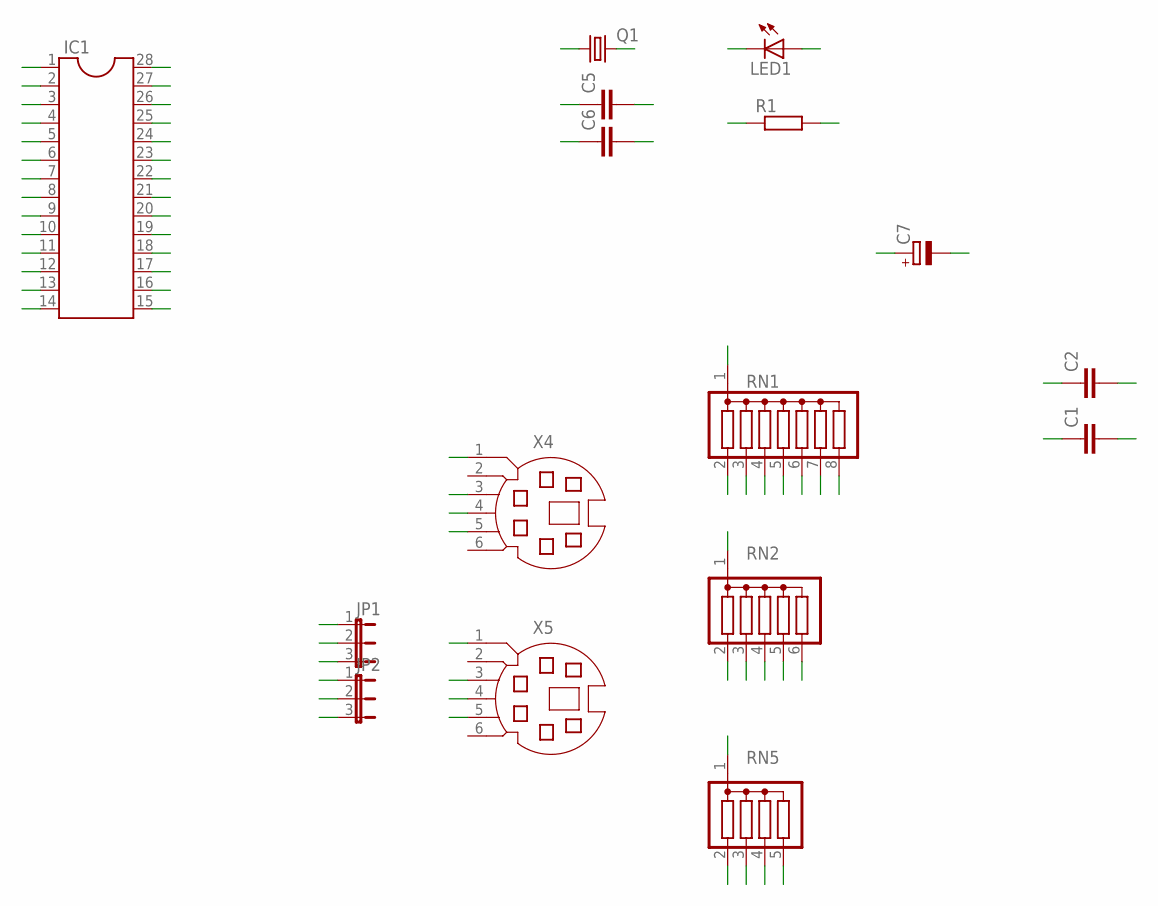
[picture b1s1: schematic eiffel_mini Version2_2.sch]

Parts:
C1, C2: C-EU025-060X050; C025-060X050
C5, C6: C-EU025-024X044; C025-024X044
C7: CPOL-EUE2,5-6E; E2,5-6E
IC1: DIL28-3
JP1, JP2: JP2E; JP2
LED1: LED3MM
Q1: CRYSTALHC49S; HC49/S
R1: R-EU_0204/7; 0204/7
RN1: G07R; SIL8
RN2: G05R; SIL6
RN5: G04R; SIL5
X4, X5: MD06S; MDIN06S

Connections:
/MCLR: IC1.1, RN1.7
GND: C1.2, C2.2, C5.2, C6.2, C7.-, IC1.8, IC1.19, JP2.2, JP2.3, LED1.K (C), X4.3, X5.3
LED: LED1.A, R1.1
RA0: IC1.2, RN1.8
RA1: IC1.3, RN1.2
RA2: IC1.4, RN1.3
RA3: IC1.5, RN1.4
RA4: IC1.6, RN1.5
RA5: IC1.7, RN1.6
RB0: IC1.21, RN5.2, X5.1
RB1: IC1.22, RN5.3, X5.5
RB2: IC1.23, RN5.4, X4.1
RB3: IC1.24, RN5.5, X4.5
RB4: IC1.25
RB5: IC1.26
RB6: IC1.27
RB7: IC1.28
RC0: IC1.11, RN2.2
RC1: IC1.12, RN2.3
RC2: IC1.13, RN2.4
RC3: IC1.14, RN2.5
RC4: IC1.15, RN2.6
RC5: IC1.16
RC6: IC1.17, JP2.1
RC7: IC1.18, JP1.3
VCC: C1.1, C2.1, C7.+, IC1.20, JP1.1, JP1.2, R1.2, RN1.1, RN2.1, RN5.1, X4.4, X5.4
XI: C5.1, IC1.9, Q1.1
XO: C6.1, IC1.10, Q1.2

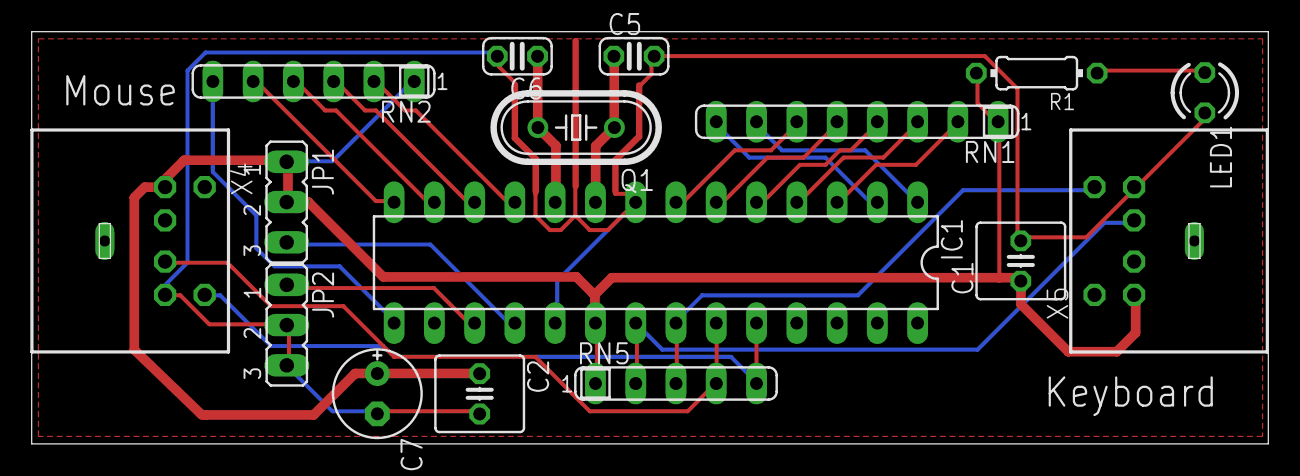
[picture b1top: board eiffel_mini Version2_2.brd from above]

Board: 2 copper layers, 78.0 x 26.0 mm, 16 parts (0 on the bottom side), 23 nets.

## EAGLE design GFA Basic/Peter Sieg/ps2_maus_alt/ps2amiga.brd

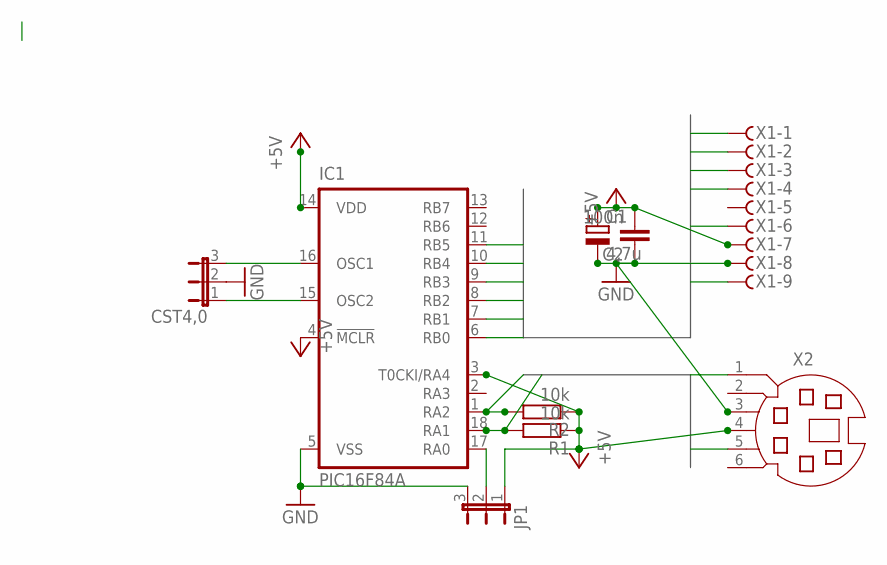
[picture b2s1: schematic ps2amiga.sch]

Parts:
C1: 4,7u; E2,5-6
C2: 100n; C025-025X050
CST4,0: JP2E; JP2
IC1: PIC16F84A; DIL18
JP1: JP2E; JP2
R1, R2: 10k; 0207/10
X1: F09HS; F09H
X2: MD06S; MDIN06S

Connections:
+5V: C1.+, C2.2, IC1.3 (T0CKI/RA4), IC1.4 (!MCLR), IC1.14 (VDD), JP1.1, R1.1, R2.1, X1.7, X2.4
A1: IC1.7 (RB1), X1.1
A2: IC1.6 (RB0), X1.2
A3: IC1.8 (RB2), X1.3
A4: IC1.9 (RB3), X1.4
A5: IC1.11 (RB5), X1.9
A6: IC1.10 (RB4), X1.6
B1: IC1.18 (RA1), R1.2, X2.1
B2: IC1.1 (RA2), R2.2, X2.5
GND: C1.-, C2.1, CST4,0.2, IC1.5 (VSS), JP1.3, X1.8, X2.3
unnamed: CST4,0.3, IC1.16 (OSC1)
unnamed: CST4,0.1, IC1.15 (OSC2)
unnamed: IC1.17 (RA0), JP1.2

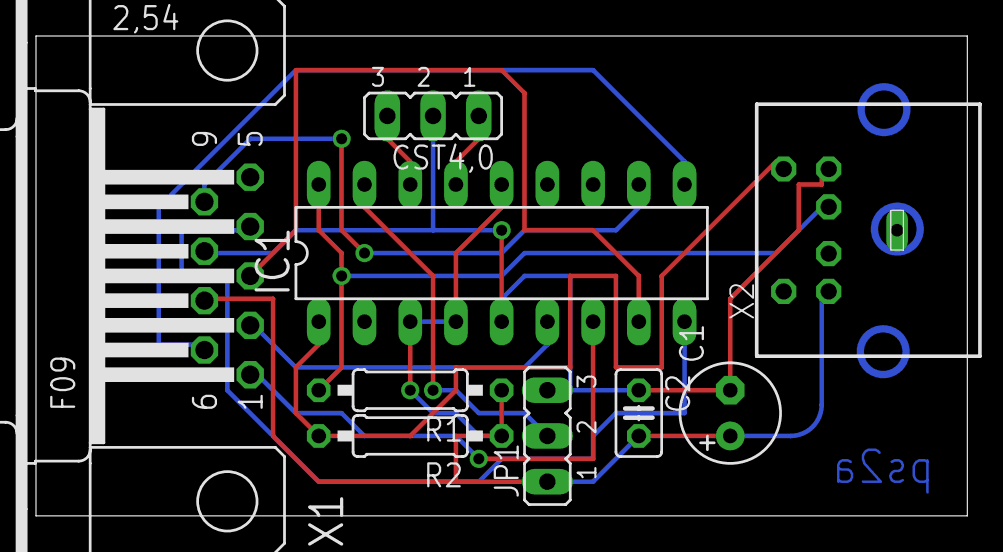
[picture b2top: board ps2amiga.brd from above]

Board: 2 copper layers, 51.7 x 26.7 mm, 9 parts (0 on the bottom side), 13 nets.

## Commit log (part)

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2019-02-23 Added Rajah's new x2 source
2019-02-23 STart magazine sources
2019-03-02 Added Maziacs source code
2019-03-02 Updated HXCFE_file_selector submodule
2019-03-10 Updated stspeech related code
2019-03-12 Added Paolo Simoes sources
2019-03-26 Sources from magazines' coverdisks
2019-03-29 Sources from magazines' coverdisks (cont'd)
2019-04-06 Examples from the Metacomco assembler
2019-04-08 Added Lotto max package
2019-04-27 Updated submodules. Replaced Peter Lane's repos with local copies since the account was zapped. Added Sqward's projects as submodules
2019-04-28 Added 2 pixel bender source
    < gloky > you must set standalone equ 1
    < gloky > interstice = 1 there is intercice
    < gloky > nbintrerstice =2 -> 4 pix of interstice
    < gloky > incbin 'file directly'
2019-05-06 Added uip tools (Christian Zietz's fork), updated submodules
2019-05-26 Added Hans Wessels' C scroll code
2019-06-03 Added Zappy's personal github repo
2019-06-05 A few sources from uncovered archives
2019-06-27 Added White Water Madness source code
2019-07-03 Added Wec Le Mans graphics files
2019-07-08 Added Satantronic's demo from Sommarhack 2019. Updated submodules
2019-07-14 Added Motus source code with kind permission from SMFX
2019-07-21 Freshly discovered sources and small tidy up
2019-07-21 Updated submodules
2019-08-01 Some new sources including Latz' lzip and Ulf Ronald Andersson's library
2019-08-05 Added latest version of Rajah's tools, updated submodules
2019-08-16 Added source code from Hotline and TLB
2019-09-20 Add a few old and new sources
2019-10-15 Added sources from Maggie issues and TOS Magazine
2019-10-18 Some sources from magazines including ST Mag
2019-10-30 Sources from ST News, ST Mag and ST User
2019-11-11 More sources from ST User
2019-11-18 Added latest Vision sources
2019-12-12 Added brand new MOD player from T.AL (!), updated submodules
2019-12-16 Added roc-hell from Dune as a submodule
2019-12-17 Added tr1x's bytetros from Sillyventure 19
2019-12-25 Added chicane's very interesting Lotus enhancements, updated submodules
2020-01-02 Added source code for Sardonic as a submodule
2020-01-15 Added Bilter timings source, Texel source (submodule) and a bunch more
2020-01-17 Added KrazyKato's source
2020-01-21 Added ULM's syncexplorer as a submodule
2020-02-08 Move files
2020-02-22 Added Christian Zietz's ideboot as a submodule, updated submodules, cleanup
2020-03-05 Added some newly found sources
2020-03-11 A few sources from magazine cover disks
2020-04-04 Removed some duplicated files - fixes #8
2020-04-04 sonolumineszenz as a submodule. Fixes #9.
2020-04-12 Added Sprell source code (with the kind permission of nerve)
2020-04-20 Some new sources
2020-05-03 New patched Bugaboo sources from Newline
2020-05-03 Added some documentation as a submodule
2020-05-14 Update submodules
2020-05-14 Added Matt Lacey's Falcon framework, updated submodules
2020-05-18 Added all known source code from Patrick Ruiz (thanks to Miro Kropáček for supplying). Closes issue #11
2020-05-31 Fixups (because Newline needs more <3)
2020-06-10 Added DML's superb agtools as a submodule
2020-06-22 Examples for tOri's ramcart (http://raven1.magix.net/stramcart/stramcart.html)
2020-06-22 The submodules, they are updated
2020-07-05 Added Synergy's "Having a period in 3D space" source code
2020-07-19 Removing submodule due to it ceased to exist
2020-07-19 Updating submodules
2020-07-27 Adding some rare codebases
2020-07-30 Added 7UP source code. Thanks to Derek John Evans for the spotting!
2020-07-30 Added gnome source. thanks to Derek John Evans for the spotting and corrections to the corrupt files!
2020-08-01 Aded latest Vision (4.7a1) sources
2020-08-01 Added Sam Nasty source code released today
2020-08-02 Added Tom's STOS syncscroll extensions
2020-08-03 Tidy up
2020-08-22 Added wrecking ball source code as a submodule
2020-08-22 Some driver sources
2020-10-04 Tidy up, some new sources
2020-10-10 More old sources, updated submodules
2020-10-10 Adding source code from older bytetros
2020-10-12 Added new submodules
2020-10-20 Added new submodule and tutorial source
2020-10-22 Added ULM's DSOTS sources
2020-11-02 Added a few Forth interpreters
2020-11-15 Updated submodules, added new music disk submodule
2020-11-15 Re-adding files from deleted (by the author) submodule
2020-12-21 Added new Vision source code
2020-12-29 New submodule, new MJJ source
2020-12-29 Added G*P's 2020 xmas demo sources
2020-12-30 Added brand new repository (POS program in 2020) and some older ones, courtesy of Markus Hoffmann. Fixes #12
2020-12-30 Added R-Disk as a submodule
2021-01-02 New submodules, updated gloky's plasma
2021-01-06 Maybe this tilme the push will work
2021-01-17 Updated submodules, added new submodules including TAL's Star Wars demo released today
2021-01-27 Added brand new MPlayer 4.08 source code, among others
2021-03-22 Added new sources, cleanups
2021-03-22 Submodule renamed (God help us all)
2021-04-08 Updated submodules, etc
2021-04-25 More old sources unearthed
2021-04-28 Added some new submodules, plus more old stuff
2021-05-24 Added new Vision version, updated submodules
2021-09-03 A few new and old things
2021-09-22 Updated submodules, new sources
2021-09-22 More submodule updating
2021-10-16 Some unearthed Inter and Animal Mine source, thanks to Questor for digging these up
2021-10-29 A few new submodules, new TTF-GDOS version, some old-new Automation source code
2021-11-23 Recently uncovered sources
2021-12-21 Added two new utilities, updated submodules
2021-12-26 Updated submodules, added some other projects
2021-12-27 Test
2021-12-31 Some new and old sources
2022-01-02 Some Omikron basic sources
2022-01-05 Added latest Vision sources, cleaned up the RG folder and added submodules
2022-01-12 Added new submodule plus STOS code submitted by the author
2022-01-21 Added Textkonverter 5.2, kindly supplied by the author
2022-01-22 Added Sigi Painter Version 98, kindly supplied by the author
2022-01-29 Mostly updated submodules
2022-01-30 Added yet another freeware GFA BASIC program supplied by the author
2022-02-08 Added newly unearthed code
2022-02-12 Added minix ST source versions
2022-02-12 Updated submodules, replaced some defunct repositories with their last known snapshot
2022-02-13 Yet another GFA utility provided by its author
2022-02-19 Removing files so they can be replaced with a submodule
2022-02-19 Reactivating submodule
2022-03-05 Some newly surfaced sources
2022-03-10 Added a bunch of source code from the Crawly Crypt CD 2
2022-03-12 Added some old sources plus a few submodules
2022-03-20 Added some newly discovered sources and submodules
2022-04-21 Cleanups, more unearthed code
2022-04-21 Some more sources from the aforementioned Uni course
2022-04-23 Some cleanups and new submodules
2022-04-23 Updated .gitmodules
2022-04-26 Added quite a few new submodules
2022-05-06 Added Lance!'s official PT replay repo
2022-05-22 Big lot of Electronic Images source
2022-06-12 New BUGABOOF version, updated submodules
2022-07-14 Some more new and recently discovered sources
2022-07-14 Sommarhack 2022 celebratory commit
2022-07-19 Added ULM code via submodules
2022-07-23 Janitorial cleanups
2022-08-01 Adding a few submodules that should have been added a long time ago
2022-08-07 Some old code, updated submodules
2022-08-15 Some old sources
2022-08-22 Updated submodules, added source from a SV22 product
2022-09-16 Updated some modules
2022-09-16 Updated submodules
    mend
2022-09-24 Added new submodule
2022-10-22 Added source code for B.A.T. II
2022-10-31 Various submodules (including Dread and B.A.T. II source) as well as some MJJ source code
2022-10-31 A few more submodules
2022-11-13 Updated submodules, plus some new source
2022-12-03 Added modified Gulam sources
2022-12-03 Updated submodules, replaced dead submodule with actual files
2022-12-30 Added some misc sources
2023-02-06 Updated submodules, added new ones, replaced dead submodules with their repo contents, some new source
2023-02-11 Added souce code for the silly demo as a submodule
2023-03-04 Updated sumbodules, added new submodule
2023-03-29 As requested
2023-04-12 Added some old sources
2023-05-08 Added some historical sources
2023-05-08 Assorted sources
2023-05-08 Added 68k inside entries, updated submodules
2023-05-23 Very old and very new sources
2023-06-19 Added submodule
2023-07-04 Added new submodule, plus some old source
2023-08-18 Updated submodules, plus a few misc sources
2023-08-24 Many old sources added
2023-09-02 Some new code, updated submodules
2023-09-22 Old source code uncovered from an old hard disk image
2023-09-23 Some more old source code
2023-10-15 Some old sources and a new submodule
2023-11-19 Updated submodules, plus a brand new one
2023-12-02 Updated submodules plus new submodule
2023-12-09 A few old sources, plus new submodule
2023-12-15 Updated submodules, some new submodules plus some code
2023-12-25 Removed offline submodule (will be replaced with the files next commit), added new submodule and sources
2023-12-25 Replaced offline submodule with the files from last fetch (closes #14)
2023-12-29 Added GemDemo sources
2024-01-02 New submodule, updated submodules
2024-01-15 Updated submodules, some new ones, plus some newly discovered code
2024-02-04 Fixed typo for submodule path
2024-02-12 Added all Gribnif Software repos as submodules
2024-02-12 Forgot to add this to the previous commit
2024-04-25 Updated submodules, some more uncovered code
2024-05-02 A few new submodules
2024-05-05 Updated submodules, some old sources
2024-05-12 New submodule, some old sources
2024-05-16 Some new source code, cleanups
2024-05-16 Cleanups
2024-05-28 New versions of all programs by Pierre Thonthat
2024-06-29 Added some new sources, cleanups
2024-06-30 Small fix
2024-07-09 Added sources from Sommarhack 2024 releases
2024-07-22 Added New Depack source code
2024-09-20 Added Source code for Elite, Leonard's 4k source, updated submodules
2024-10-13 add missing files in chip_mus and scroller, remove desktop.inf, rename readme, notes and two .run files
2024-11-04 Updated submodule, added new submodule
2024-11-11 New submodule
2024-11-23 Moving some files
2024-11-27 Adding the Vroom source code
2024-12-04 Adding Sillyventure releases
2024-12-06 Adding some stuff
2024-12-23 Added submodule for FaSTEr, plus some other stuff
2024-12-27 Added some old code
2024-12-27 Updated submodules, some old source
2025-01-02 Updated submodules, some new old code
2025-01-04 Cleanups. Some old code
2025-01-04 Re-added some submodules that were mysteriously deleted
2025-01-12 Updated submodules, re-added raven suibmodule
2025-01-16 Some old sources, cleanup
2025-01-26 Some old code
2025-02-12 Fix submodule
2025-02-17 Delete Omikron Basic/rockyone/mi-3.346 directory
    version obsolète
2025-03-09 Cleanups, some new submodules
2025-03-09 Added a lot of sources from ST Computer cover disks
2025-03-09 Added more sources from ST Computer
2025-03-09 Updted submodules, added some old sources
2025-04-01 Last bunch of source code from ST Computer magazines
2025-04-05 Midi Maze decomiped source, cleanups, some old sources
2025-04-06 Updated submodules, some old code
2025-04-17 Added tools courtesy of Overlanders
2025-04-17 Some old source
2025-05-02 Create file
2025-05-02 serpent (#24)
    * Delete Omikron Basic/rockyone directory
    * Delete Omikron Basic/Serpent directory
2025-05-06 Added the Cyberpunks' demo from Sillyventure, some old sources and cleanups
2025-05-26 Added Doom8088ST as submodule, updated submodules
2025-07-07 Cleanups, old sources, new stuff from Sommarhack 2025
2025-07-12 Added more releases from Sommarhack 2025 as well as some old source
2025-09-21 Hopefully fixed some submodules
2025-11-09 Updated submodules, removed deleted source
2025-11-11 Added Rings Of Medusa II source code, some old sources
2025-12-19 New version of vision, added more old source code
2025-12-29 Fixes for some of the submodules
2026-01-13 Added babaliba sources
2026-02-06 Updated submodules, new submodule
2026-02-15 Updated submodules, some new source
2026-04-05 Updated submodules, cleanups
2026-04-09 Updated submodules, some new sources
2026-05-02 New submodules, some old code, updated submodules
2026-05-07 New submodule, some old source
2026-05-07 Updated submodules, new submodules, some old source
